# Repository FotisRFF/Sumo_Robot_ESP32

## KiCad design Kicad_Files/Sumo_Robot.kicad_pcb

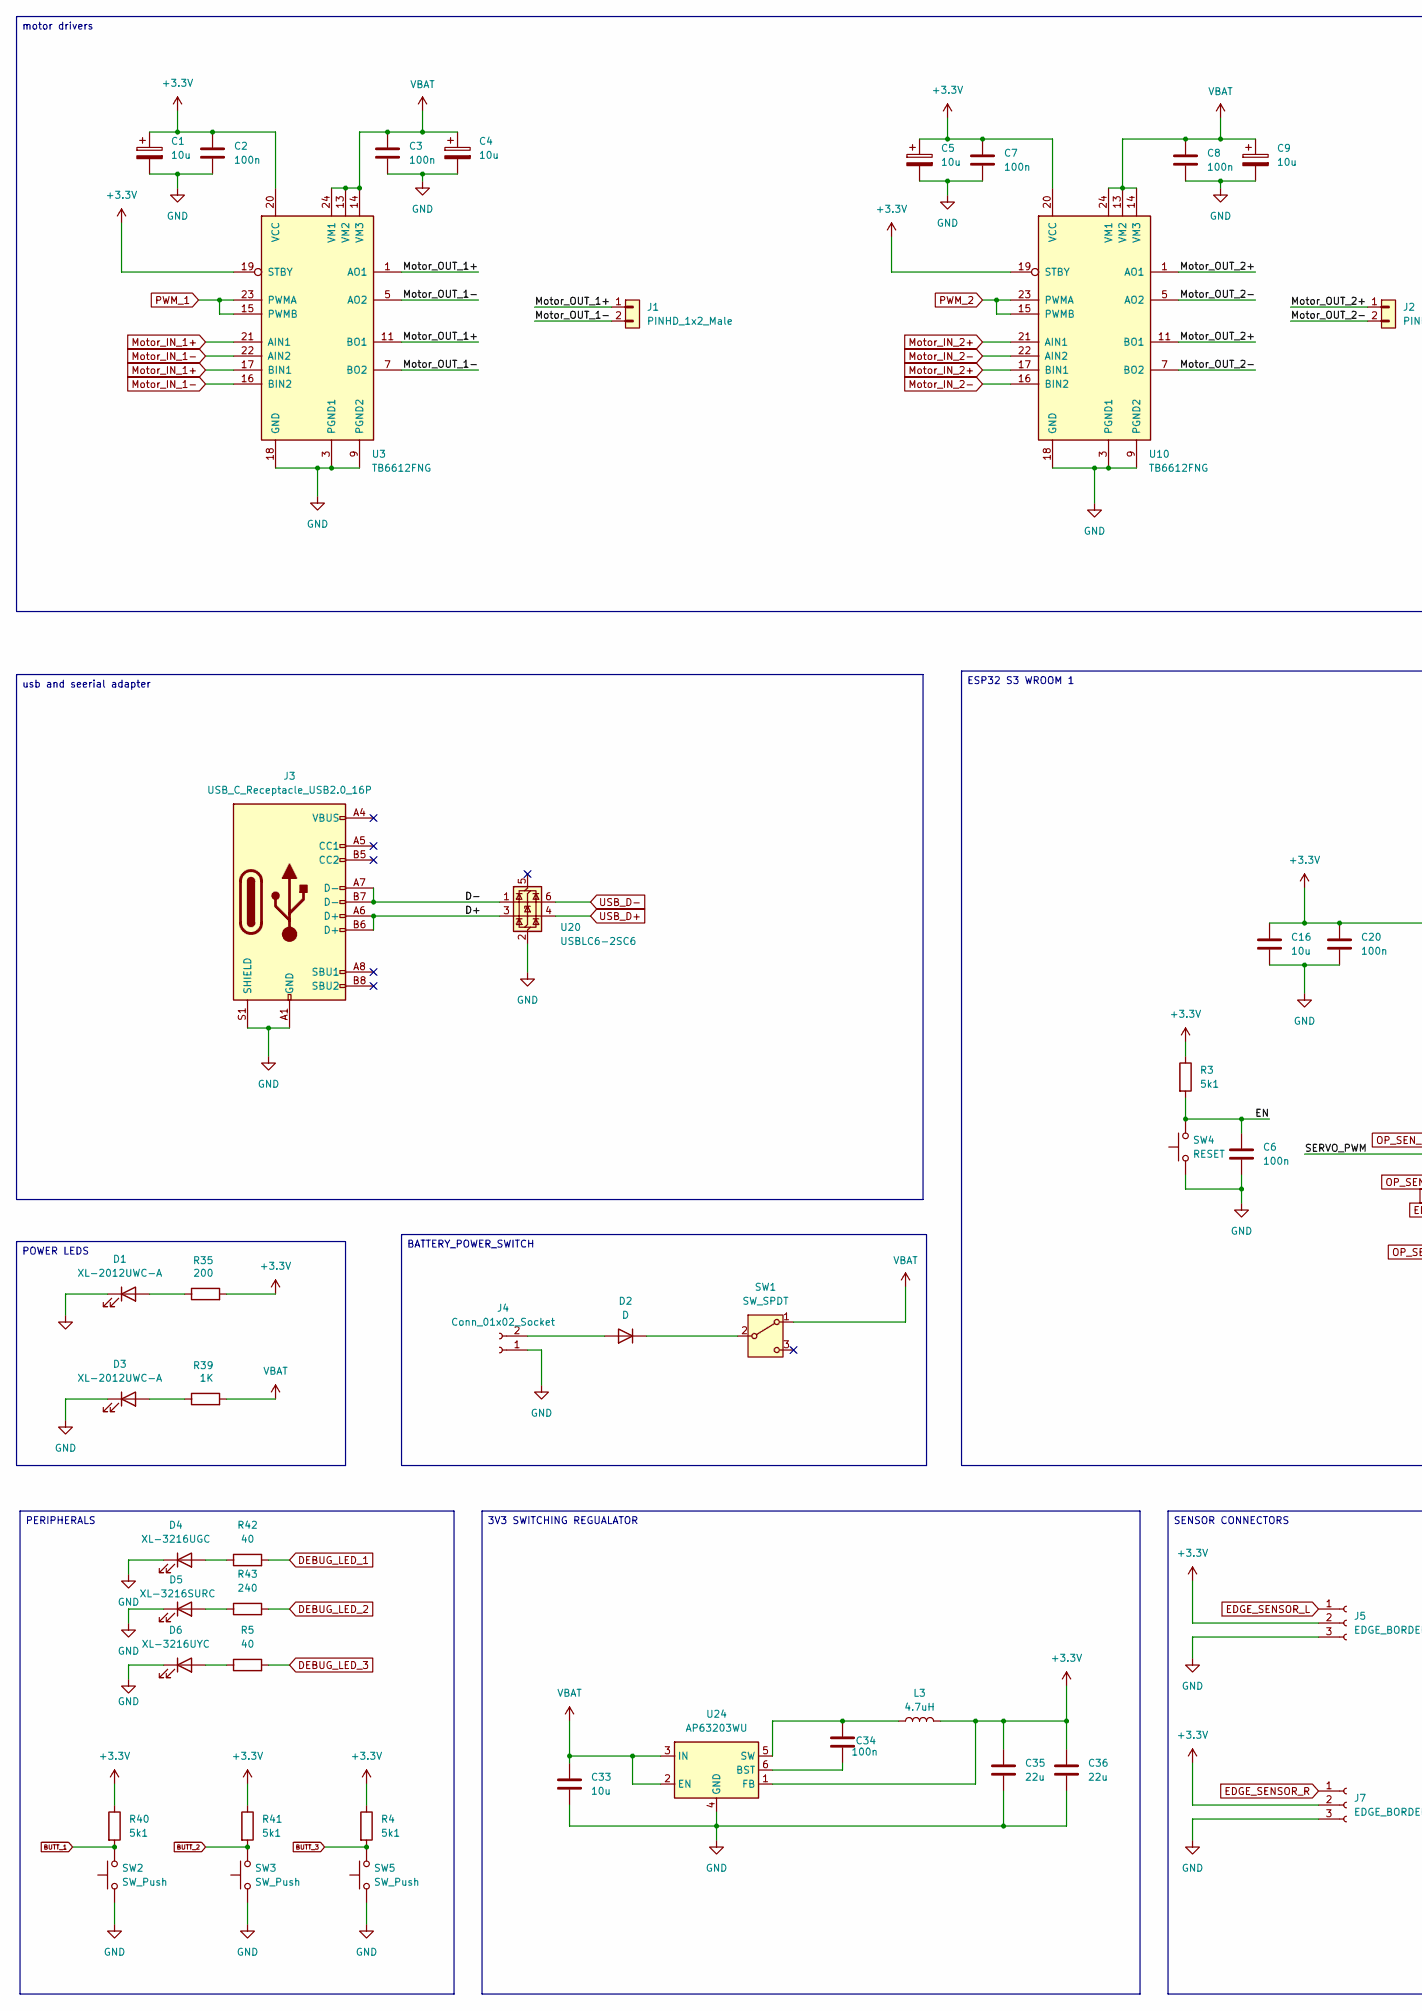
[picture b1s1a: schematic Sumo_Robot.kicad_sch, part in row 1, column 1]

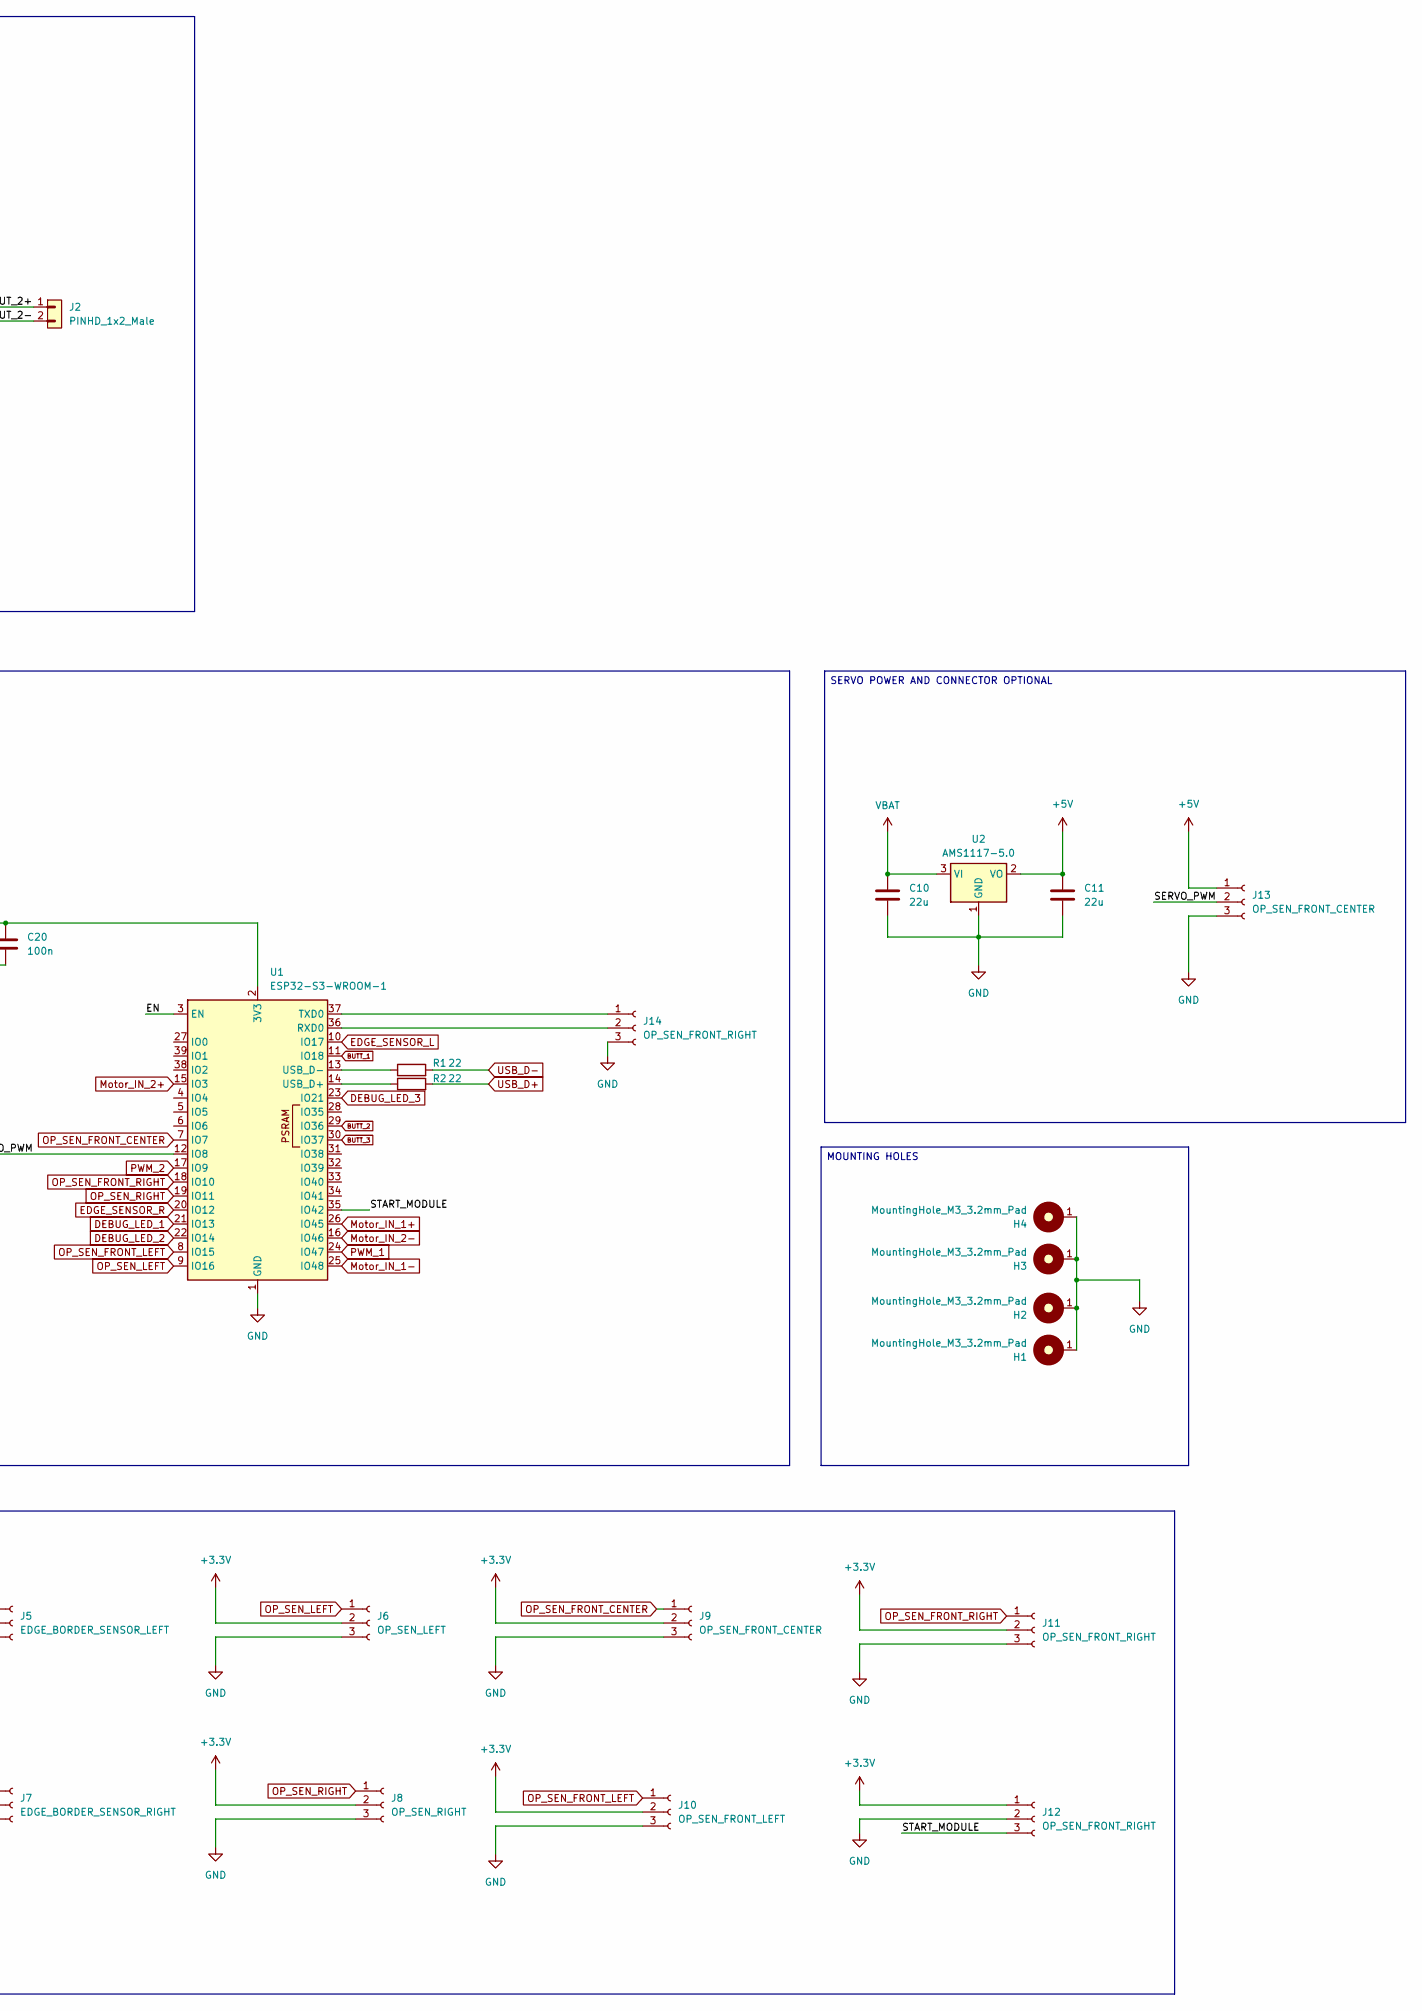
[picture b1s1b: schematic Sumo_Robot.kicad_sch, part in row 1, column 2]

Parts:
C1, C4, C5, C9: 10u; CP_EIA-1608-08_AVX-J_HandSolder
C2, C3, C7, C8: 100n; C_0805_2012Metric
C6: 100n; C_0805_2012Metric_Pad1.18x1.45mm_HandSolder
C10, C11, C35, C36: 22u; C_0805_2012Metric
C16: 10u; C_0805_2012Metric_Pad1.18x1.45mm_HandSolder
C20: 100n; C_0402_1005Metric
C33: 10u; C_0805_2012Metric
C34: 100n; C_0402_1005Metric_Pad0.74x0.62mm_HandSolder
D1, D3: XL-2012UWC-A; LED_0805_2012Metric_Pad1.15x1.40mm_HandSolder
D2: D; D_1206_3216Metric_Pad1.42x1.75mm_HandSolder
D4: XL-3216UGC; LED_1206_3216Metric
D5: XL-3216SURC; LED_1206_3216Metric
D6: XL-3216UYC; LED_1206_3216Metric
H1, H2, H3, H4: MountingHole_M3_3.2mm_Pad; MountingHole_3.2mm_Pad
J1, J2: PINHD_1x2_Male; PinHeader_1x02_P2.54mm_Vertical
J3: USB_C_Receptacle_USB2.0_16P; USB_C_Receptacle_GCT_USB4105-xx-A_16P_TopMnt_Horizontal
J4: Conn_01x02_Socket; PinHeader_1x02_P2.54mm_Vertical
J5: EDGE_BORDER_SENSOR_LEFT; PinHeader_1x03_P2.54mm_Vertical
J6: OP_SEN_LEFT; PinHeader_1x03_P2.54mm_Vertical
J7: EDGE_BORDER_SENSOR_RIGHT; PinHeader_1x03_P2.54mm_Vertical
J8: OP_SEN_RIGHT; PinHeader_1x03_P2.54mm_Vertical
J9, J13: OP_SEN_FRONT_CENTER; PinHeader_1x03_P2.54mm_Vertical
J10: OP_SEN_FRONT_LEFT; PinHeader_1x03_P2.54mm_Vertical
J11, J12, J14: OP_SEN_FRONT_RIGHT; PinHeader_1x03_P2.54mm_Vertical
L3: 4.7uH; L_Sunlord_MWSA0402S
R1, R2: 22; R_0402_1005Metric_Pad0.72x0.64mm_HandSolder
R3, R4, R40, R41: 5k1; R_0805_2012Metric_Pad1.20x1.40mm_HandSolder
R5, R42: 40; R_0805_2012Metric_Pad1.20x1.40mm_HandSolder
R35: 200; R_0805_2012Metric
R39: 1K; R_0805_2012Metric
R43: 240; R_0805_2012Metric_Pad1.20x1.40mm_HandSolder
SW1: SW_SPDT; SW_Slide-03_Wuerth-WS-SLTV_10x2.5x6.4_P2.54mm
SW2, SW3, SW5: SW_Push; SW_PUSH_6mm_H13mm
SW4: RESET; SW_PUSH_6mm_H13mm
U1: ESP32-S3-WROOM-1
U2: AMS1117-5.0; SOT-223-3_TabPin2
U3, U10: TB6612FNG; SSOP-24_5.3x8.2mm_P0.65mm
U20: USBLC6-2SC6; SOT-23-6
U24: AP63203WU; TSOT-23-6

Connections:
+3.3V: C1.1, C2.1, C5.1, C7.1, C16.2, C20.2, C35.1, C36.1, J5.2, J6.2, J7.2, J8.2, J9.2, J10.2, J11.2, J12.1, L3.2, R3.1, R4.1, R35.2, R40.1, R41.1, U1.2 (3V3), U3.19 (STBY), U3.20 (VCC), U10.19 (STBY), U10.20 (VCC), U24.1 (FB)
+5V: C11.1, J13.1, U2.2 (VO)
/D+: J3.A6 (D+), J3.B6 (D+), U20.3 (I/O2)
/D-: J3.A7 (D-), J3.B7 (D-), U20.1 (I/O1)
/EN: C6.2, R3.2, SW4.2, U1.3 (EN)
/Motor_OUT_1+: J1.1, U3.1 (AO1), U3.2 (AO1), U3.11 (BO1), U3.12 (BO1)
/Motor_OUT_1-: J1.2, U3.5 (AO2), U3.6 (AO2), U3.7 (BO2), U3.8 (BO2)
/Motor_OUT_2+: J2.1, U10.1 (AO1), U10.2 (AO1), U10.11 (BO1), U10.12 (BO1)
/Motor_OUT_2-: J2.2, U10.5 (AO2), U10.6 (AO2), U10.7 (BO2), U10.8 (BO2)
/SERVO_PWM: J13.2, U1.12 (IO8)
/START_MODULE: J12.3, U1.35 (IO42)
BUTT_1: R40.2, SW2.2, U1.11 (IO18)
BUTT_2: R41.2, SW3.2, U1.29 (IO36)
BUTT_3: R4.2, SW5.2, U1.30 (IO37)
DEBUG_LED_1: R42.2, U1.21 (IO13)
DEBUG_LED_2: R43.2, U1.22 (IO14)
DEBUG_LED_3: R5.2, U1.23 (IO21)
EDGE_SENSOR_L: J5.1, U1.10 (IO17)
EDGE_SENSOR_R: J7.1, U1.20 (IO12)
GND: C1.2, C2.2, C3.2, C4.2, C5.2, C6.1, C7.2, C8.2, C9.2, C10.2, C11.2, C16.1, C20.1, C33.2, C35.2, C36.2, D1.1 (K), D3.1 (K), D4.1 (K), D5.1 (K), D6.1 (K), H1.1, H2.1, H3.1, H4.1, J3.A1 (GND), J3.A12 (GND), J3.B1 (GND), J3.B12 (GND), J3.S1 (SHIELD), J4.1, J5.3, J6.3, J7.3, J8.3, J9.3, J10.3, J11.3, J12.2, J13.3, J14.3, SW2.1, SW3.1, SW4.1, SW5.1, U1.1 (GND), U1.40 (GND), U1.41 (GND), U2.1 (GND), U3.3 (PGND1), U3.4 (PGND1), U3.9 (PGND2), U3.10 (PGND2), U3.18 (GND), U10.3 (PGND1), U10.4 (PGND1), U10.9 (PGND2), U10.10 (PGND2), U10.18 (GND), U20.2 (GND), U24.4 (GND)
Motor_IN_1+: U1.26 (IO45), U3.17 (BIN1), U3.21 (AIN1)
Motor_IN_1-: U1.25 (IO48), U3.16 (BIN2), U3.22 (AIN2)
Motor_IN_2+: U1.15 (IO3), U10.17 (BIN1), U10.21 (AIN1)
Motor_IN_2-: U1.16 (IO46), U10.16 (BIN2), U10.22 (AIN2)
unnamed: D1.2 (A), R35.1
unnamed: D2.2 (A), J4.2
unnamed: D2.1 (K), SW1.2 (B)
unnamed: D3.2 (A), R39.1
unnamed: D4.2 (A), R42.1
unnamed: D5.2 (A), R43.1
unnamed: D6.2 (A), R5.1
unnamed: J14.1, U1.37 (TXD0)
unnamed: J14.2, U1.36 (RXD0)
unnamed: R2.1, U1.14 (USB_D+)
unnamed: R1.1, U1.13 (USB_D-)
unnamed: C34.2, U24.6 (BST)
unnamed: C34.1, L3.1, U24.5 (SW)
OP_SEN_FRONT_CENTER: J9.1, U1.7 (IO7)
OP_SEN_FRONT_LEFT: J10.1, U1.8 (IO15)
OP_SEN_FRONT_RIGHT: J11.1, U1.18 (IO10)
OP_SEN_LEFT: J6.1, U1.9 (IO16)
OP_SEN_RIGHT: J8.1, U1.19 (IO11)
PWM_1: U1.24 (IO47), U3.15 (PWMB), U3.23 (PWMA)
PWM_2: U1.17 (IO9), U10.15 (PWMB), U10.23 (PWMA)
USB_D+: R2.2, U20.4 (I/O2)
USB_D-: R1.2, U20.6 (I/O1)
VBAT: C3.1, C4.1, C8.1, C9.1, C10.1, C33.1, R39.2, SW1.1 (A), U2.3 (VI), U3.13 (VM2), U3.14 (VM3), U3.24 (VM1), U10.13 (VM2), U10.14 (VM3), U10.24 (VM1), U24.2 (EN), U24.3 (IN)

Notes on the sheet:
SENSOR CONNECTORS
POWER LEDS
SERVO POWER AND CONNECTOR OPTIONAL
usb and seerial adapter
motor drivers
PERIPHERALS
MOUNTING HOLES
ESP32 S3 WROOM 1
BATTERY_POWER_SWITCH
3V3 SWITCHING REGUALATOR

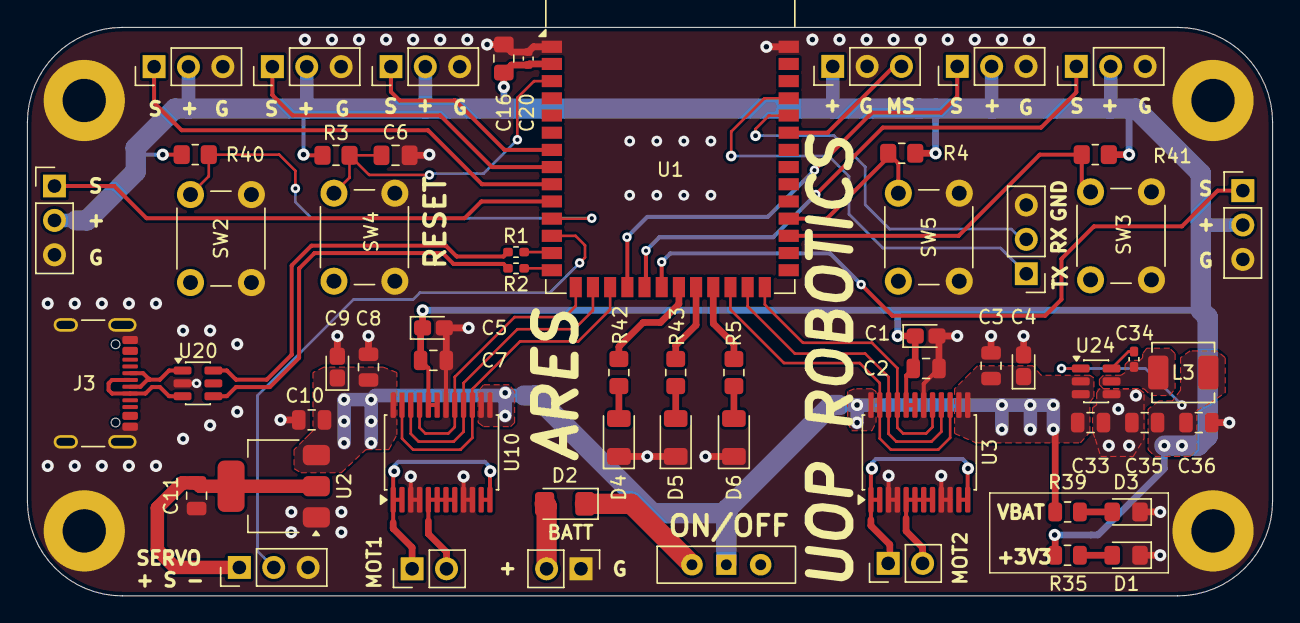
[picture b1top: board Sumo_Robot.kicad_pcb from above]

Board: 4 copper layers, 92.0 x 42.0 mm, 64 parts (0 on the bottom side), 47 nets.

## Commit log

2025-12-17 Create test
